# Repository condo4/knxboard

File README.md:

# KnxBoard

A compact 4-layer PCB that connects an STM32 microcontroller to the KNX home automation bus via the NCN5130 transceiver IC.

## Overview

KnxBoard integrates an STM32G491KEU6 (ARM Cortex-M4, 170 MHz) with an NCN5130MNTWG KNX TP transceiver. The NCN5130 handles the KNX physical and MAC layers and provides on-board power regulation from the KNX bus voltage, so the board requires no external power supply when connected to a KNX installation.

**Board version:** V5.0  
**PCB size:** 35.75 × 33.75 mm, 4 layers, 1.6 mm thickness  
**Manufactured by:** JLCPCB

## Key Components

| Reference | Part | Description |
|-----------|------|-------------|
| IC1 | STM32G491KEU6 | ARM Cortex-M4, 170 MHz, 512 KB Flash, 112 KB SRAM, UFQFPN32 |
| IC2 | NCN5130MNTWG | KNX certified TP transceiver (TP1-256), 9600 Bd, integrated DC-DC |
| Y1 | 16 MHz crystal | MCU clock source |
| D1 | SS16T3G | Schottky diode |
| D2 | SMAJ40CA | 40 V bidirectional TVS, KNX bus protection |
| D3 | LED | KNX programming indicator |
| SW1 | Push button | KNX programming button |

## Connectors

| Reference | Function |
|-----------|----------|
| J1 | KNX bus (2-pin) |
| J2 | SWD debug/programming (2×3) |
| J3 | RS485 / 1-Wire interface (10-pin) |
| J4 | Auxiliary / expansion (10-pin) |

## MCU Pin Assignment

| Signal | Pin | Peripheral | Description |
|--------|-----|------------|-------------|
| KNX_TX | PA2 | LPUART1_TX | KNX data transmit to NCN5130 |
| KNX_RX | PA3 | LPUART1_RX | KNX data receive from NCN5130 |
| KNX_PROG_BTN | PA0 | GPIO_Input | Programming mode button |
| KNX_SAVEB | PA1 | GPIO_Input | Save-B input from NCN5130 |
| KNX_PROG_LED | PF1 | GPIO_Output | Programming mode LED |
| RS437/W1_TX | PA9 | USART1_TX | RS485 / 1-Wire transmit |
| RS437/W1_RX | PA10 | USART1_RX | RS485 / 1-Wire receive |
| DEBUG_TX | PB3 | USART2_TX | Debug UART transmit |
| DEBUG_RX | PA15 | USART2_RX | Debug UART receive |
| SWDIO | PA13 | SYS_JTMS | SWD data |
| SWCLK | PA14 | SYS_JTCK | SWD clock |

ADC2 monitors internal signals (bus voltage/current supervision via NCN5130).

## Power Architecture

The NCN5130 converts KNX bus voltage (21–29 V DC) internally:

- **DC-DC1:** Fixed 3.3 V — powers the STM32 and board logic
- **DC-DC2:** Adjustable 1.2–21 V — configurable auxiliary rail
- **Linear regulator:** 20 V — internal NCN5130 supply

The board draws up to 40 mA from the KNX bus.

## PCB Stackup

| Layer | Function |
|-------|----------|
| F.Cu | Signal + components (all 44 footprints on front) |
| In1.Cu | Ground plane |
| In2.Cu | Power plane (3.3 V / 12 V) |
| B.Cu | Signal |

## Firmware

The `CubeMX/` directory contains the STM32CubeMX project (`CubeMX.ioc`) used to generate HAL initialization code.

- **Toolchain:** GCC / Makefile
- **HAL package:** STM32Cube FW_G4 V1.5.1
- **Active peripherals:** LPUART1 (KNX), USART1 (RS485/1-Wire), USART2 (debug), TIM6, ADC2, SWD

## Repository Structure

```
KnxBoard/
├── KnxBoard.kicad_sch       # Schematic
├── KnxBoard.kicad_pcb       # PCB layout
├── KnxBoard.kicad_pro       # KiCad project
├── CubeMX/                  # STM32CubeMX project
│   └── CubeMX.ioc
├── Library.pretty/          # Custom KiCad footprints
│   ├── NCN5130MNTWG.kicad_mod
│   └── STM32G491KEU6.kicad_mod
├── datasheet/               # Component datasheets
├── JLCPCB_KNXBOARD_V5.0_1.zip  # Gerbers / manufacturing files
└── KnxBoard-backups/        # KiCad auto-backups
```

## Tools

- [KiCad 9](https://www.kicad.org/) — schematic and PCB design
- [STM32CubeMX 6.8](https://www.st.com/en/development-tools/stm32cubemx.html) — MCU peripheral configuration
- [STM32CubeIDE](https://www.st.com/en/development-tools/stm32cubeide.html) or `arm-none-eabi-gcc` — firmware build

## References

- [NCN5130 Datasheet](datasheet/NCN5130-D.PDF)
- [STM32G491KE Datasheet](datasheet/STM32G491KE_Datasheet.pdf)
- [STM32G491KE Reference Manual](datasheet/STM32G491KE_RefManual.pdf)

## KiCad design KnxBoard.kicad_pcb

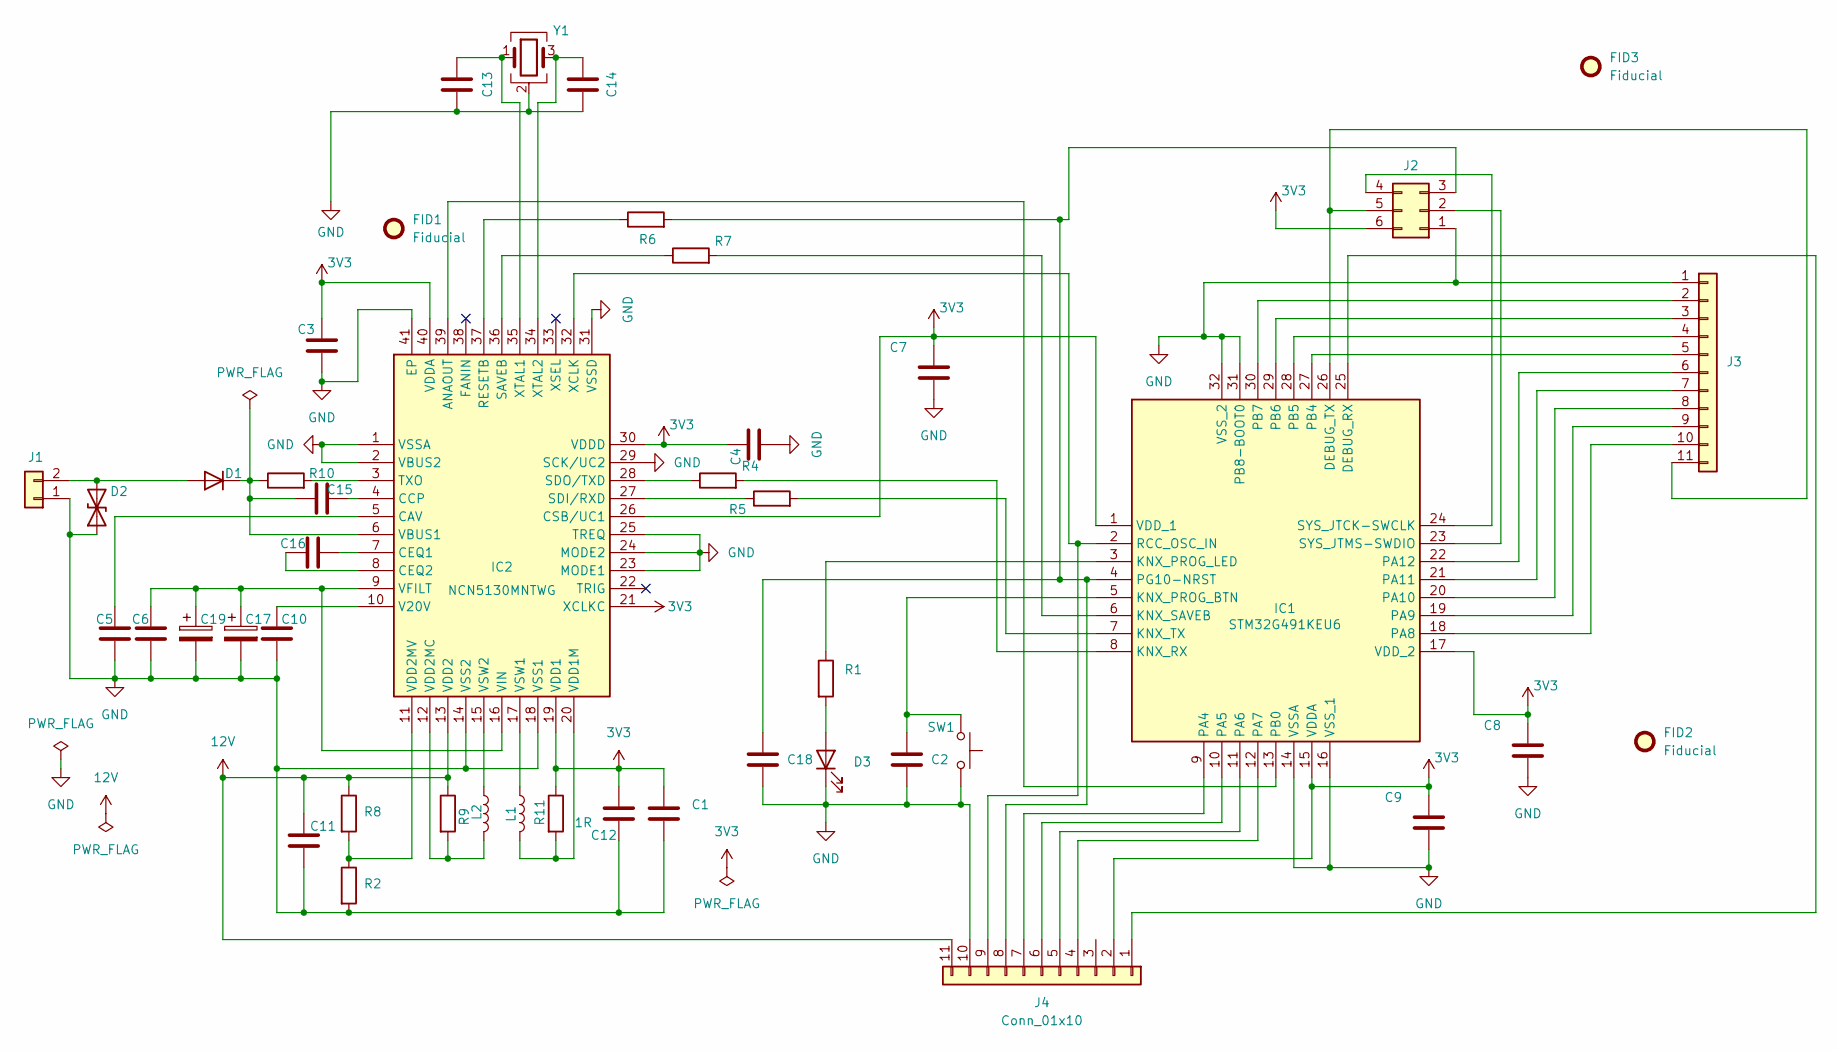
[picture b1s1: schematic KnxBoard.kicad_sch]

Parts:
C1, C2, C3, C4, C5, C6, C7, C8, C9, C18: 0.1 uF 50 VDC 5% 0402 X7S; C_0402_1005Metric; Mouser Part Number 81-GRM155C71H104JE9D
C10: 1 uF 100 VDC 10% 0805 X7S; C_0805_2012Metric; Mouser Part Number 81-GRJ21BC72A105KE1L
C11: 22 uF 25 VDC 0805 X5R; C_0805_2012Metric; Mouser Part Number 81-GRM21BC71C106KE1K
C12: 10 uF 16 VDC 10% 0805 X7S; C_0805_2012Metric; Mouser Part Number 81-GRM21BC71C106KE1K
C13, C14: 10 pF 50 VDC 5% 0402 C0G; C_0402_1005Metric; Mouser Part Number 81-GRM1555C1H100JA01D
C15: 0.047 uF 50 VDC 5% 0402 X7S; C_0402_1005Metric; Mouser Part Number 81-GRM155C71H473JE9D
C16: 0.22 uF 50 VDC 10% 0805 X7R; C_0805_2012Metric; Mouser Part Number 81-GCM21BR71H224KA7K
C17, C19: 100uF 35 Volt; CP_Elec_6.3x7.7; Mouser Part Number 661-EMZA350A101MF80S
D1: SS16T3G; D_SMA; Mouser Part Number 863-SS16T3G
D2: SMAJ40CA; D_SMA; Mouser Part Number 652-SMAJ40CA
D3: LED; LED_0603_1608Metric; Mouser Part Number 710-150060RS55040
FID1, FID2, FID3: Fiducial; Fiducial_1mm_Mask2mm
IC1: STM32G491KEU6; UQFN-32_5x5mm_P0.5mm; Mouser Part Number 511-STM32G491KEU6
IC2: NCN5130MNTWG; QFN50P600X600X100-41N; Manufacturer_Part_Number NCN5130MNTWG; Mouser Part Number 863-NCN5130MNTWG
J1: Conn_01x02; KNX_Connector
J2: Conn_02x03_Counter_Clockwise; PinHeader_2x03_P1.27mm_Vertical
J3, J4: Conn_01x10; PinHeader_1x11_P2.54mm_Vertical
L1, L2: 220 uH 0.4A; L_1008_2520Metric; Mouser Part Number 963-LB2518T221M
R1: 100; R_0402_1005Metric; Mouser Part Number 594-MCS04020C1000FE0
R2: 20k; R_0402_1005Metric; Mouser Part Number 594-MCS04020C2002FE0
R4, R5, R6, R7: 0; R_0402_1005Metric; Mouser Part Number 594-MCS04020Z0000ZE0
R8: 180k; R_0402_1005Metric; Mouser Part Number 594-MCS04020C1803FE0
R9, R11: 1R; R_0402_1005Metric; Mouser Part Number 594-MCS0402MC1008FE5
R10: 27 1W; R_2512_6332Metric; Mouser Part Number 660-WK73R2BTTD27R0F
SW1: SW_Push; SW_SPST_SKQG_WithStem; Mouser Part Number 688-SKQGAB
Y1: 16MHz; Crystal_SMD_3225-4Pin_3.2x2.5mm; Mouser Part Number 732-FA238-16B-K3

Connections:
3V3: C1.1, C3.1, C4.1, C7.1, C8.1, C9.1, C12.1, IC1.1 (VDD_1), IC1.15 (VDDA), IC1.17 (VDD_2), IC2.19 (VDD1), IC2.21 (XCLKC), IC2.26 (CSB/UC1), IC2.30 (VDDD), IC2.40 (VDDA), J2.6, J4.2, R11.1
12V: C11.1, IC2.13 (VDD2), J4.11, R8.1, R9.1
GND: C1.2, C2.2, C3.2, C4.2, C5.2, C6.2, C7.2, C8.2, C9.2, C10.2, C11.2, C12.2, C13.2, C14.2, C17.2, C18.2, C19.2, D2.1 (A1), D3.1 (K), IC1.14 (VSSA), IC1.16 (VSS_1), IC1.31 (PB8-BOOT0), IC1.32 (VSS_2), IC2.1 (VSSA), IC2.2 (VBUS2), IC2.14 (VSS2), IC2.18 (VSS1), IC2.23 (MODE1), IC2.24 (MODE2), IC2.25 (TREQ), IC2.29 (SCK/UC2), IC2.31 (VSSD), IC2.41 (EP), J1.1, J2.1, J3.1, J4.10, R2.2, SW1.2, Y1.2 (G), Y1.4 (G)
unnamed: D1.2 (A), D2.2 (A2), J1.2
unnamed: C15.1, D1.1 (K), IC2.6 (VBUS1), R10.1
unnamed: D3.2 (A), R1.2
unnamed: IC1.25 (DEBUG_RX), J4.1
unnamed: IC1.26 (DEBUG_TX), J2.5, J3.11
unnamed: C2.1, IC1.5 (KNX_PROG_BTN), SW1.1
unnamed: IC1.3 (KNX_PROG_LED), R1.1
unnamed: IC1.8 (KNX_RX), R4.2
unnamed: IC1.6 (KNX_SAVEB), R7.2
unnamed: IC1.7 (KNX_TX), R5.2
unnamed: IC1.9 (PA4), J4.7
unnamed: IC1.10 (PA5), J4.6
unnamed: IC1.11 (PA6), J4.5
unnamed: IC1.12 (PA7), J4.4
unnamed: IC1.18 (PA8), J3.10
unnamed: IC1.19 (PA9), J3.9
unnamed: IC1.20 (PA10), J3.8
unnamed: IC1.21 (PA11), J3.7
unnamed: IC1.22 (PA12), J3.6
unnamed: IC1.13 (PB0), IC2.39 (ANAOUT)
unnamed: IC1.27 (PB4), J3.5
unnamed: IC1.28 (PB5), J3.4
unnamed: IC1.29 (PB6), J3.3
unnamed: IC1.30 (PB7), J3.2
unnamed: C18.1, IC1.4 (PG10-NRST), J2.3, J4.8, R6.2
unnamed: IC1.2 (RCC_OSC_IN), IC2.32 (XCLK), J4.9
unnamed: IC1.24 (SYS_JTCK-SWCLK), J2.4
unnamed: IC1.23 (SYS_JTMS-SWDIO), J2.2
unnamed: C5.1, IC2.5 (CAV)
unnamed: C15.2, IC2.4 (CCP)
unnamed: C16.2, IC2.7 (CEQ1)
unnamed: C16.1, IC2.8 (CEQ2)
unnamed: IC2.37 (RESETB), R6.1
unnamed: IC2.36 (SAVEB), R7.1
unnamed: IC2.27 (SDI/RXD), R5.1
unnamed: IC2.28 (SDO/TXD), R4.1
unnamed: IC2.3 (TXO), R10.2
unnamed: C10.1, IC2.10 (V20V)
unnamed: IC2.20 (VDD1M), L1.2, R11.2
unnamed: IC2.12 (VDD2MC), L2.2, R9.2
unnamed: IC2.11 (VDD2MV), R2.1, R8.2
unnamed: C6.1, C17.1, C19.1, IC2.9 (VFILT), IC2.16 (VIN)
unnamed: IC2.17 (VSW1), L1.1
unnamed: IC2.15 (VSW2), L2.1
unnamed: C13.1, IC2.35 (XTAL1), Y1.1
unnamed: C14.1, IC2.34 (XTAL2), Y1.3

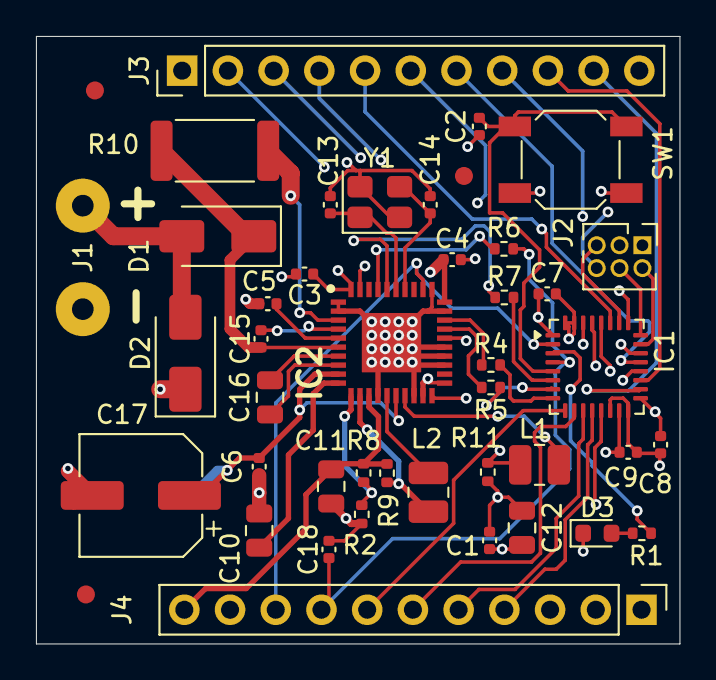
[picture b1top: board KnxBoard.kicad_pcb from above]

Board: 4 copper layers, 35.8 x 33.8 mm, 45 parts (1 on the bottom side), 49 nets.

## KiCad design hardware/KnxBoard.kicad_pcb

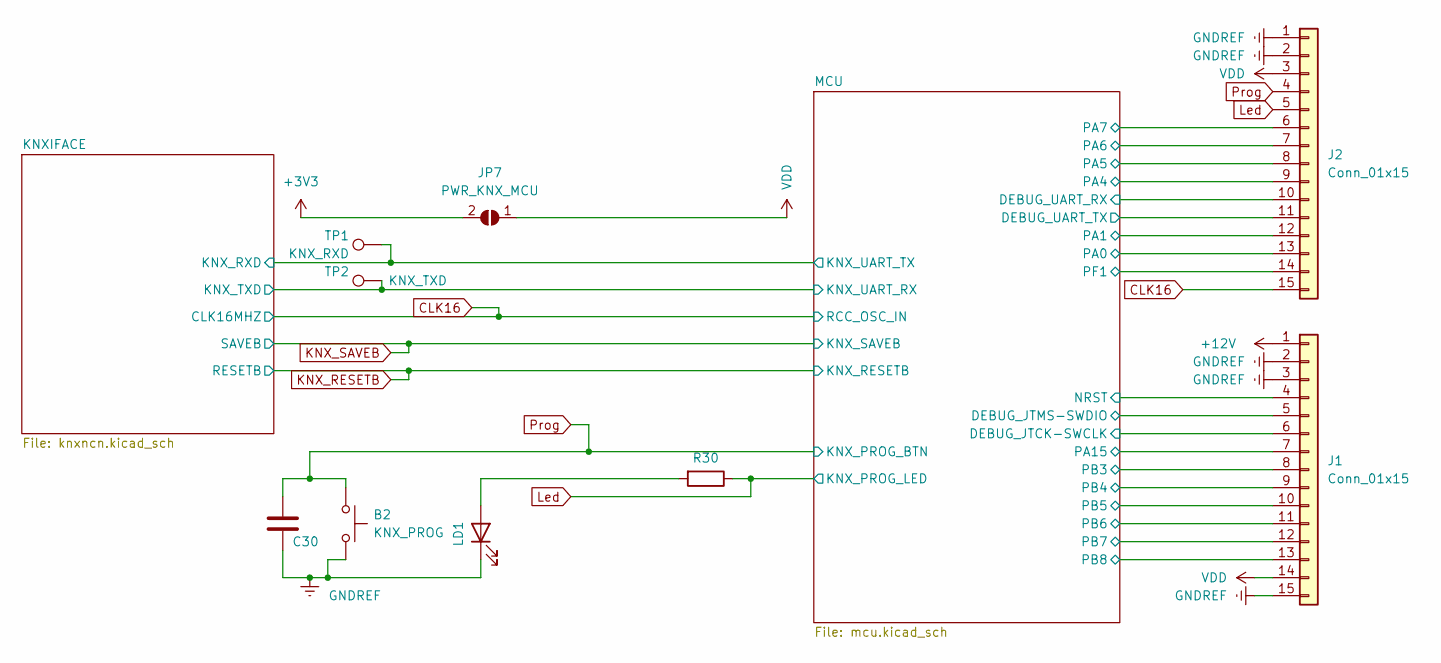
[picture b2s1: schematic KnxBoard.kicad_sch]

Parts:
B2: KNX_PROG; SW_SPST_SKQG_WithStem
C30: 100nF 6.3V; C_0603_1608Metric_Pad1.08x0.95mm_HandSolder; MPN CL10B104KA8NNWC
J1, J2: Conn_01x15; PinHeader_1x15_P2.54mm_Vertical
JP7: PWR_KNX_MCU; SolderJumper-2_P1.3mm_Open_TrianglePad1.0x1.5mm
LD1: LED; LED_0603_1608Metric; MPN 150060RS55040
R30: 100R; R_0603_1608Metric; MPN MCT06030C1000FP500
TP1: KNX_RXD; TestPoint_Pad_D1.0mm
TP2: KNX_TXD; TestPoint_Pad_D1.0mm

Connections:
+3V3: JP7.2 (B); also elsewhere on the board
+12V: J1.1; also elsewhere on the board
/KNXIFACE/KNX_RXD: TP1.1; also elsewhere on the board
/KNXIFACE/KNX_TXD: TP2.1; also elsewhere on the board
/MCU/DEBUG_JTCK-SWCLK: J1.6; also elsewhere on the board
/MCU/DEBUG_JTMS-SWDIO: J1.5; also elsewhere on the board
/MCU/DEBUG_UART_RX: J2.10; also elsewhere on the board
/MCU/DEBUG_UART_TX: J2.11; also elsewhere on the board
/MCU/NRST: J1.4; also elsewhere on the board
/MCU/PA0: J2.13; also elsewhere on the board
/MCU/PA1: J2.12; also elsewhere on the board
/MCU/PA4: J2.9; also elsewhere on the board
/MCU/PA5: J2.8; also elsewhere on the board
/MCU/PA6: J2.7; also elsewhere on the board
/MCU/PA7: J2.6; also elsewhere on the board
/MCU/PA15: J1.7; also elsewhere on the board
/MCU/PB3: J1.8; also elsewhere on the board
/MCU/PB4: J1.9; also elsewhere on the board
/MCU/PB5: J1.10; also elsewhere on the board
/MCU/PB6: J1.11; also elsewhere on the board
/MCU/PB7: J1.12; also elsewhere on the board
/MCU/PB8: J1.13; also elsewhere on the board
/MCU/PF1: J2.14; also elsewhere on the board
CLK16: J2.15; also elsewhere on the board
GNDREF: B2.2, C30.2, J1.2, J1.3, J1.15, J2.1, J2.2, LD1.1 (K); also elsewhere on the board
Led: J2.5, R30.1; also elsewhere on the board
unnamed: LD1.2 (A), R30.2
Prog: B2.1, C30.1, J2.4; also elsewhere on the board
VDD: J1.14, J2.3, JP7.1 (A); also elsewhere on the board

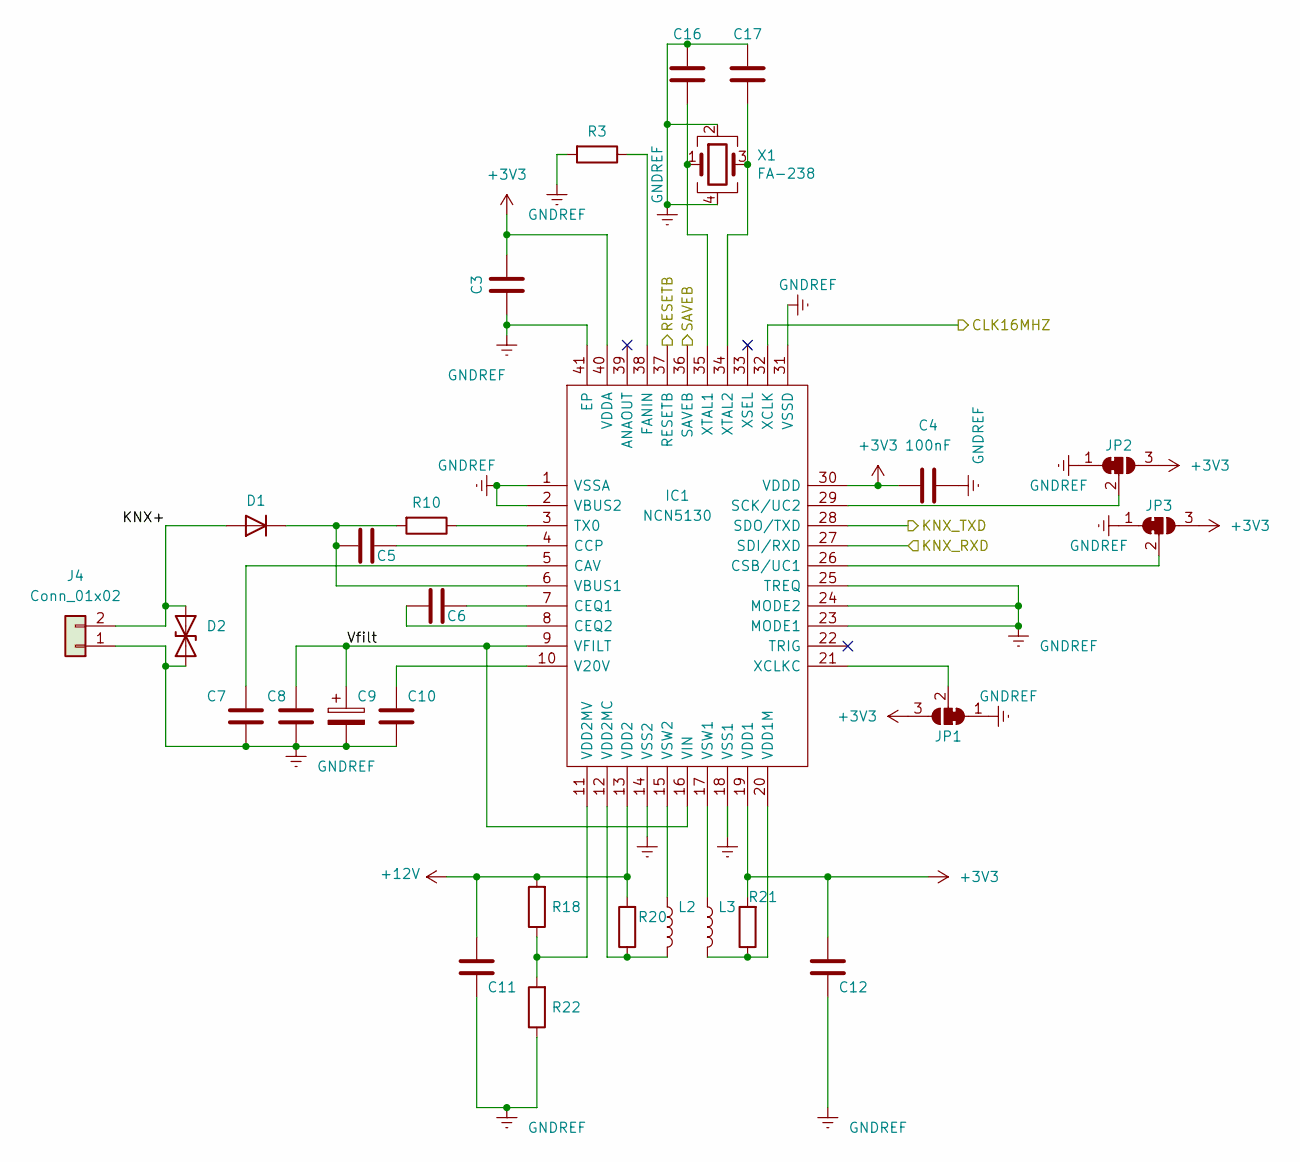
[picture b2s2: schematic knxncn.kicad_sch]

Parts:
C3: 100nF 6.3V; C_0603_1608Metric_Pad1.08x0.95mm_HandSolder; MPN CL10B104KA8NNWC
C4: 100nF; C_0603_1608Metric_Pad1.08x0.95mm_HandSolder
C5: 47nF 50V; C_0603_1608Metric_Pad1.08x0.95mm_HandSolder; MPN CL10B473KB8NNND
C6: 220nF 50V; C_0603_1608Metric_Pad1.08x0.95mm_HandSolder; MPN CL10A224KB8NNNC
C7, C8: 100nF 50V; C_0603_1608Metric_Pad1.08x0.95mm_HandSolder; MPN CL10B104KB8NFNC
C9: 100uF 35V; CP_Elec_6.3x7.7
C10: 1uF 50V ESR < 2ohm; C_0603_1608Metric_Pad1.08x0.95mm_HandSolder; MPN CL10A105KL8NNNC
C11, C12: 10uF 6.3V ESR < 0.1ohm; C_0805_2012Metric_Pad1.18x1.45mm_HandSolder; MPN CL21A106KOQNNNG
C16, C17: 10pF 6.3V; C_0603_1608Metric_Pad1.08x0.95mm_HandSolder; MPN CL10C100DB81PNC
D1: SS16T3G; D_SMA; MPN SS16T3G
D2: 1SMA40CA; D_SMA
IC1: NCN5130; Manufacturer_Part_Number NCN5130; Mouser Part Number N/A
J4: Conn_01x02; KNX_Connector
JP1: Clock_8_16; SolderJumper-3_P1.3mm_Open_RoundedPad1.0x1.5mm
JP2: Parity; SolderJumper-3_P1.3mm_Open_RoundedPad1.0x1.5mm
JP3: Speed; SolderJumper-3_P1.3mm_Open_RoundedPad1.0x1.5mm
L2, L3: 220uH; L_1008_2520Metric; MPN LB2518T221M
R3: NOTMOUNT; R_0603_1608Metric
R10: 27R 1W; R_0612_1632Metric; MPN WK73R2BTTD27R0F
R18: 56K 1/16w; R_0603_1608Metric; MPN RT0603DRE0756KL
R20, R21: 1R 1/16W; R_0603_1608Metric; MPN SFR03EZPJ1R0
R22: 499K 1/16w; R_0603_1608Metric; MPN RT0603FRE07499KL
X1: FA-238; Crystal_SMD_SeikoEpson_FA238-4Pin_3.2x2.5mm; MPN FA-238 16.0000MB-K3

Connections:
+3V3: C3.2, C4.1, C12.1, IC1.19 (VDD1), IC1.30 (VDDD), IC1.40 (VDDA), JP1.3 (B), JP2.3 (B), JP3.3 (B), R21.2; also elsewhere on the board
+12V: C11.1, IC1.13 (VDD2), R18.2, R20.2; also elsewhere on the board
/KNXIFACE/KNX+: D1.2 (A), D2.2 (A2), J4.2
/KNXIFACE/KNX_RXD: IC1.27 (SDI/RXD); also elsewhere on the board
/KNXIFACE/KNX_TXD: IC1.28 (SDO/TXD); also elsewhere on the board
/KNXIFACE/Vfilt: C8.1, C9.1, IC1.9 (VFILT), IC1.16 (VIN)
CLK16: IC1.32 (XCLK); also elsewhere on the board
GNDREF: C3.1, C4.2, C7.2, C8.2, C9.2, C10.2, C11.2, C12.2, C16.1, C17.1, D2.1 (A1), IC1.1 (VSSA), IC1.2 (VBUS2), IC1.14 (VSS2), IC1.18 (VSS1), IC1.23 (MODE1), IC1.24 (MODE2), IC1.25 (TREQ), IC1.31 (VSSD), IC1.41 (EP), J4.1, JP1.1 (A), JP2.1 (A), JP3.1 (A), R3.2, R22.1, X1.2, X1.4; also elsewhere on the board
KNX_RESETB: IC1.37 (RESETB); also elsewhere on the board
KNX_SAVEB: IC1.36 (SAVEB); also elsewhere on the board
unnamed: C5.1, IC1.4 (CCP)
unnamed: C5.2, D1.1 (K), IC1.6 (VBUS1), R10.2
unnamed: C6.1, IC1.7 (CEQ1)
unnamed: C6.2, IC1.8 (CEQ2)
unnamed: C7.1, IC1.5 (CAV)
unnamed: C10.1, IC1.10 (V20V)
unnamed: C16.2, IC1.35 (XTAL1), X1.1
unnamed: C17.2, IC1.34 (XTAL2), X1.3
unnamed: IC1.3 (TX0), R10.1
unnamed: IC1.11 (VDD2MV), R18.1, R22.2
unnamed: IC1.12 (VDD2MC), L2.2, R20.1
unnamed: IC1.15 (VSW2), L2.1
unnamed: IC1.17 (VSW1), L3.1
unnamed: IC1.20 (VDD1M), L3.2, R21.1
unnamed: IC1.21 (XCLKC), JP1.2 (C)
unnamed: IC1.26 (CSB/UC1), JP3.2 (C)
unnamed: IC1.29 (SCK/UC2), JP2.2 (C)
unnamed: IC1.38 (FANIN), R3.1

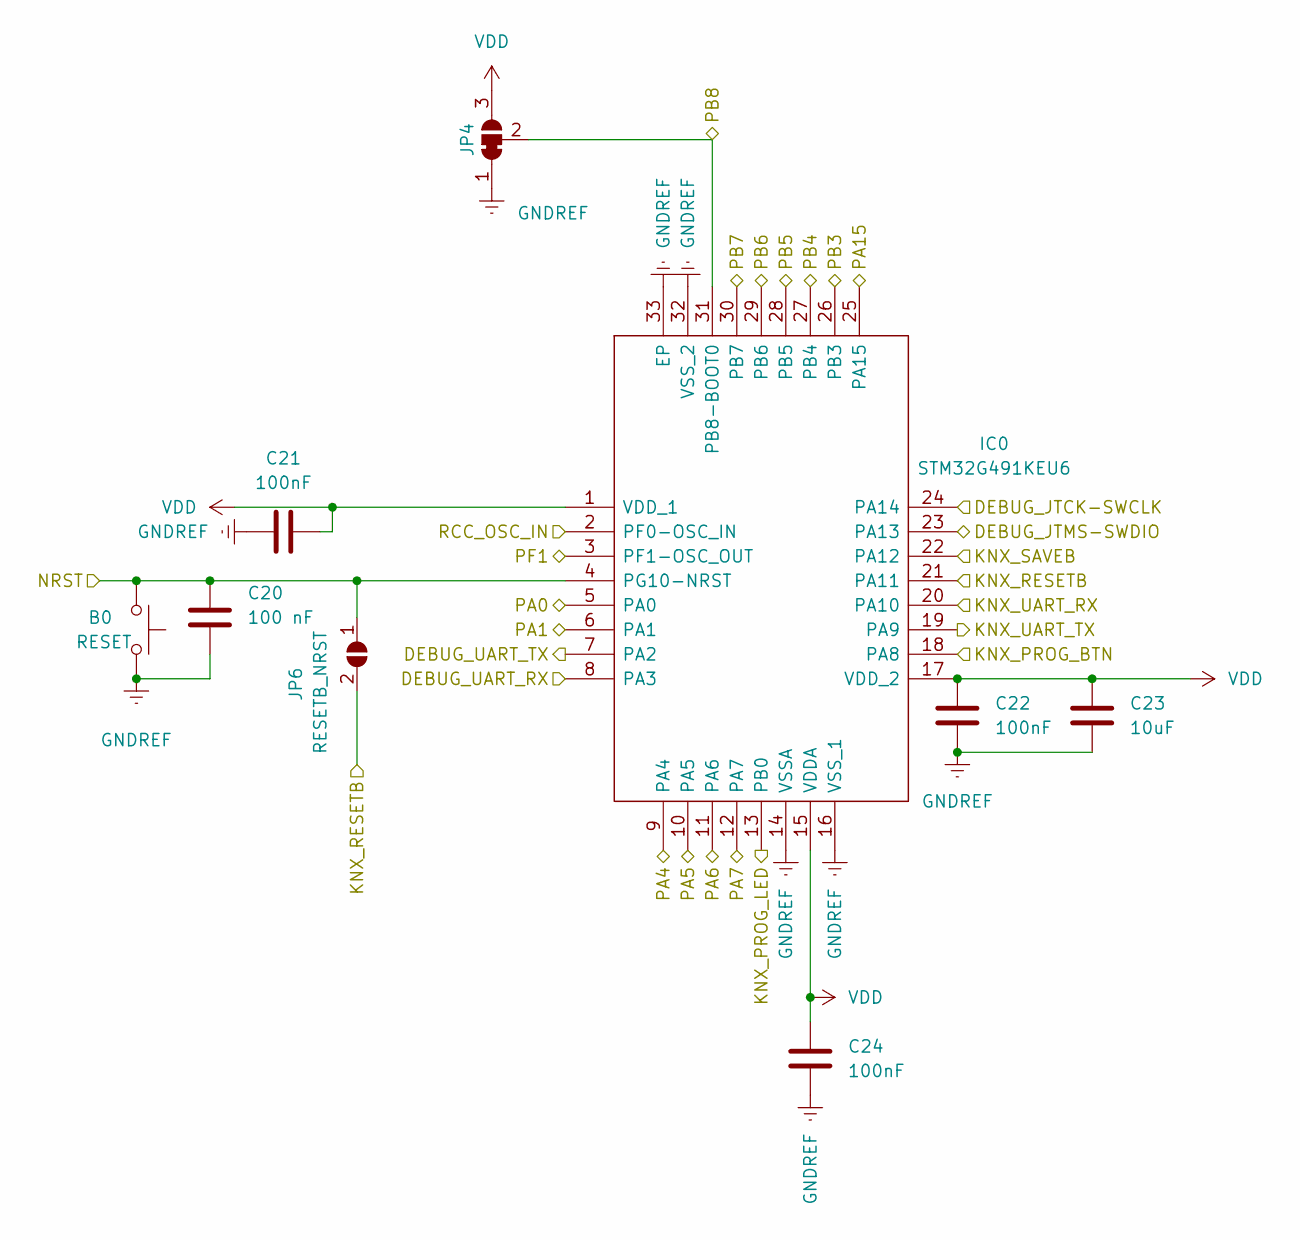
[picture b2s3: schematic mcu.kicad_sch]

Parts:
B0: RESET; SW_SPST_SKQG_WithStem
C20: 100 nF; C_0603_1608Metric_Pad1.08x0.95mm_HandSolder
C21, C22, C24: 100nF; C_0603_1608Metric_Pad1.08x0.95mm_HandSolder
C23: 10uF; C_0603_1608Metric_Pad1.08x0.95mm_HandSolder
IC0: STM32G491KEU6; QFN50P500X500X60-33N-D; Mouser Part Number 511-STM32G491KEU6
JP4: BootMode; SolderJumper-3_P1.3mm_Open_RoundedPad1.0x1.5mm
JP6: RESETB_NRST; SolderJumper-2_P1.3mm_Open_TrianglePad1.0x1.5mm

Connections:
/KNXIFACE/KNX_RXD: IC0.19 (PA9); also elsewhere on the board
/KNXIFACE/KNX_TXD: IC0.20 (PA10); also elsewhere on the board
/MCU/DEBUG_JTCK-SWCLK: IC0.24 (PA14); also elsewhere on the board
/MCU/DEBUG_JTMS-SWDIO: IC0.23 (PA13); also elsewhere on the board
/MCU/DEBUG_UART_RX: IC0.8 (PA3); also elsewhere on the board
/MCU/DEBUG_UART_TX: IC0.7 (PA2); also elsewhere on the board
/MCU/NRST: B0.1, C20.1, IC0.4 (PG10-NRST), JP6.1 (A); also elsewhere on the board
/MCU/PA0: IC0.5 (PA0); also elsewhere on the board
/MCU/PA1: IC0.6 (PA1); also elsewhere on the board
/MCU/PA4: IC0.9 (PA4); also elsewhere on the board
/MCU/PA5: IC0.10 (PA5); also elsewhere on the board
/MCU/PA6: IC0.11 (PA6); also elsewhere on the board
/MCU/PA7: IC0.12 (PA7); also elsewhere on the board
/MCU/PA15: IC0.25 (PA15); also elsewhere on the board
/MCU/PB3: IC0.26 (PB3); also elsewhere on the board
/MCU/PB4: IC0.27 (PB4); also elsewhere on the board
/MCU/PB5: IC0.28 (PB5); also elsewhere on the board
/MCU/PB6: IC0.29 (PB6); also elsewhere on the board
/MCU/PB7: IC0.30 (PB7); also elsewhere on the board
/MCU/PB8: IC0.31 (PB8-BOOT0), JP4.2 (C); also elsewhere on the board
/MCU/PF1: IC0.3 (PF1-OSC_OUT); also elsewhere on the board
CLK16: IC0.2 (PF0-OSC_IN); also elsewhere on the board
GNDREF: B0.2, C20.2, C21.1, C22.2, C23.2, C24.2, IC0.14 (VSSA), IC0.16 (VSS_1), IC0.32 (VSS_2), IC0.33 (EP), JP4.1 (A); also elsewhere on the board
KNX_RESETB: IC0.21 (PA11), JP6.2 (B); also elsewhere on the board
KNX_SAVEB: IC0.22 (PA12); also elsewhere on the board
Led: IC0.13 (PB0); also elsewhere on the board
Prog: IC0.18 (PA8); also elsewhere on the board
VDD: C21.2, C22.1, C23.1, C24.1, IC0.1 (VDD_1), IC0.15 (VDDA), IC0.17 (VDD_2), JP4.3 (B); also elsewhere on the board

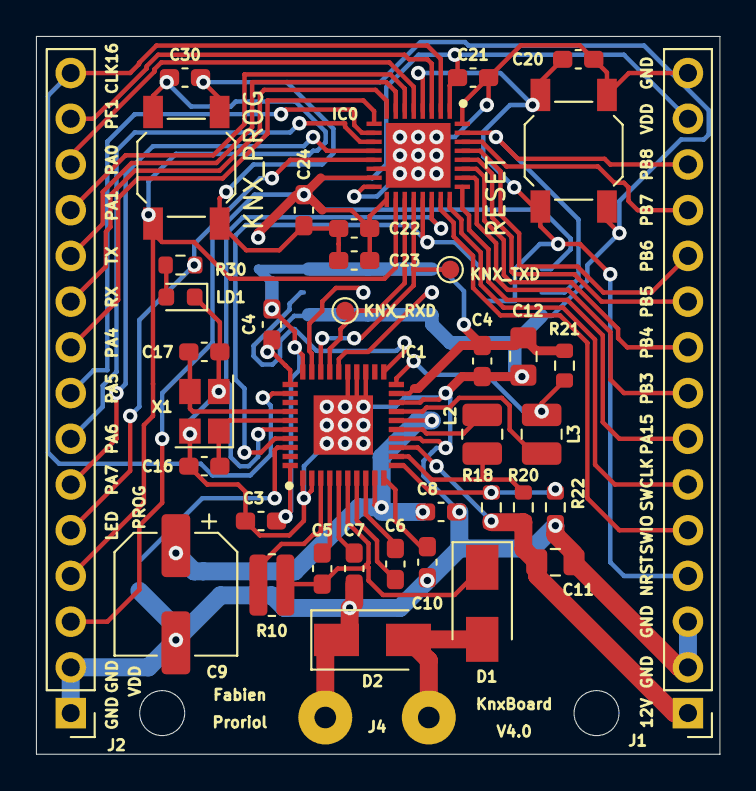
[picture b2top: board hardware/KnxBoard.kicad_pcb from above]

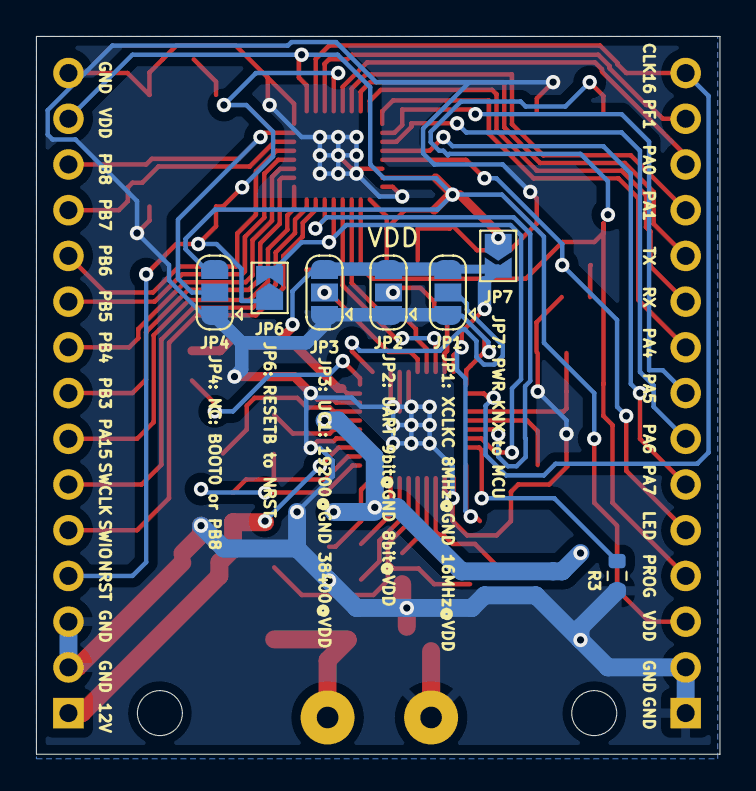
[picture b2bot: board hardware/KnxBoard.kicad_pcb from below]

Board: 2 copper layers, 38.0 x 39.9 mm, 47 parts (7 on the bottom side), 51 nets.

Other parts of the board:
C4#2: 100nF; C_0603_1608Metric_Pad1.08x0.95mm_HandSolder

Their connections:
+3V3: C4#2.1; also elsewhere on the board
GNDREF: C4#2.2; also elsewhere on the board

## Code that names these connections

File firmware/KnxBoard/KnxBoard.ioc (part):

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Mcu.Name=STM32G491K(C-E)Ux
Mcu.Package=UFQFPN32
Mcu.UserName=STM32G491KEUx
PA10.Mode=Asynchronous
PA10.Signal=USART1_RX
PA11.GPIOParameters=GPIO_Label
PA11.GPIO_Label=KNX_RESETB
PA11.Signal=GPXTI11
PA12.GPIOParameters=GPIO_Label
PA12.GPIO_Label=KNX_SAVEB
PA12.Signal=GPXTI12
PA13.Mode=JTAG_5_pins
PA13.Signal=SYS_JTMS-SWDIO
PA14.Mode=JTAG_5_pins
PA14.Signal=SYS_JTCK-SWCLK
PA15.Mode=JTAG_5_pins
PA15.Signal=SYS_JTDI
PA2.Mode=Asynchronous
PA2.Signal=USART2_TX
PA3.Mode=Asynchronous
PA3.Signal=USART2_RX
PA8.GPIOParameters=GPIO_Label
PA8.GPIO_Label=KNX_PROG_BTN
PA8.Signal=GPXTI8
PA9.Mode=Asynchronous
PA9.Signal=USART1_TX
PB0.GPIOParameters=GPIO_Label
PB0.GPIO_Label=KNX_PROG_LED
PB0.Signal=GPIO_Output
PB3.Mode=JTAG_5_pins
PB3.Signal=SYS_JTDO-SWO
PB4.Mode=JTAG_5_pins
PB4.Signal=SYS_JTRST
PF0-OSC_IN.Mode=HSE-External-Clock-Source
PF0-OSC_IN.Signal=RCC_OSC_IN
RCC.HSE_VALUE=8000000
RCC.SYSCLKFreq_VALUE=16000000
board=custom

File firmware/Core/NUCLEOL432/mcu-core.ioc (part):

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Mcu.Name=STM32L432K(B-C)Ux
Mcu.Package=UFQFPN32
Mcu.UserName=STM32L432KCUx
PA0.GPIOParameters=GPIO_Label
PA0.GPIO_Label=MCO [High speed clock in]
PA0.Mode=HSE-External-Clock-Source-for-LittleOrca
PA0.Signal=RCC_CK_IN
PA10.GPIOParameters=GPIO_Speed,GPIO_Label
PA10.GPIO_Label=KNX_RX
PA10.GPIO_Speed=GPIO_SPEED_FREQ_MEDIUM
PA10.Mode=Asynchronous
PA10.Signal=USART1_RX
PA11.GPIOParameters=GPIO_PuPd,GPIO_Label
PA11.GPIO_Label=KNX_PROG_BTN
PA11.GPIO_PuPd=GPIO_PULLDOWN
PA11.Signal=GPXTI11
PA13\ (JTMS-SWDIO).GPIOParameters=GPIO_Label
PA13\ (JTMS-SWDIO).GPIO_Label=SWDIO
PA13\ (JTMS-SWDIO).Mode=Serial_Wire
PA13\ (JTMS-SWDIO).Signal=SYS_JTMS-SWDIO
PA14\ (JTCK-SWCLK).GPIOParameters=GPIO_Label
PA14\ (JTCK-SWCLK).GPIO_Label=SWCLK
PA14\ (JTCK-SWCLK).Mode=Serial_Wire
PA14\ (JTCK-SWCLK).Signal=SYS_JTCK-SWCLK
PA15\ (JTDI).GPIOParameters=GPIO_Label
PA15\ (JTDI).GPIO_Label=DEBUG_RX
PA15\ (JTDI).Mode=Asynchronous
PA15\ (JTDI).Signal=USART2_RX
PA2.GPIOParameters=GPIO_Label
PA2.GPIO_Label=DEBUG_TX
PA2.Mode=Asynchronous
PA2.Signal=USART2_TX
PA3.Signal=ADCx_IN8
PA4.Signal=ADCx_IN9
PA5.Signal=ADCx_IN10
PA6.Signal=ADCx_IN11
PA9.GPIOParameters=GPIO_Speed,GPIO_Label
PA9.GPIO_Label=KNX_TX
PA9.GPIO_Speed=GPIO_SPEED_FREQ_MEDIUM
PA9.Mode=Asynchronous
PA9.Signal=USART1_TX
PB3\ (JTDO-TRACESWO).GPIOParameters=GPIO_Label
PB3\ (JTDO-TRACESWO).GPIO_Label=KNX_PROG_LED
PB3\ (JTDO-TRACESWO).Signal=GPIO_Output
PC14-OSC32_IN\ (PC14).Mode=LSE-External-Oscillator
PC14-OSC32_IN\ (PC14).Signal=RCC_OSC32_IN
PC15-OSC32_OUT\ (PC15).Mode=LSE-External-Oscillator
PC15-OSC32_OUT\ (PC15).Signal=RCC_OSC32_OUT
RCC.HSE_VALUE=8000000
RCC.SYSCLKFreq_VALUE=64000000
RCC.SYSCLKSource=RCC_SYSCLKSOURCE_PLLCLK
board=NUCLEO-L432KC
boardIOC=true

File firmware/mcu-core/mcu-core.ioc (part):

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Mcu.Name=STM32U575CITx
Mcu.Package=LQFP48
Mcu.UserName=STM32U575CITx
PA10.GPIOParameters=GPIO_Label
PA10.GPIO_Label=DEBUG_UART_RX
PA10.Mode=Asynchronous
PA10.Signal=USART1_RX
PA13\ (JTMS/SWDIO).Mode=JTAG_5_pins
PA13\ (JTMS/SWDIO).Signal=DEBUG_JTMS-SWDIO
PA14\ (JTCK/SWCLK).Mode=JTAG_5_pins
PA14\ (JTCK/SWCLK).Signal=DEBUG_JTCK-SWCLK
PA15\ (JTDI).Mode=JTAG_5_pins
PA15\ (JTDI).Signal=DEBUG_JTDI
PA2.GPIOParameters=GPIO_Label
PA2.GPIO_Label=KNX_UART_TX
PA2.Mode=Asynchronous
PA2.Signal=USART2_TX
PA3.GPIOParameters=GPIO_Label
PA3.GPIO_Label=KNX_UART_RX
PA3.Mode=Asynchronous
PA3.Signal=USART2_RX
PA9.GPIOParameters=GPIO_Label
PA9.GPIO_Label=DEBUG_UART_TX
PA9.Mode=Asynchronous
PA9.Signal=USART1_TX
PB10.Signal=GPXTI10
PB2.Signal=GPXTI2
PB3\ (JTDO/TRACESWO).Mode=JTAG_5_pins
PB3\ (JTDO/TRACESWO).Signal=DEBUG_JTDO-SWO
PB4\ (NJTRST).Mode=JTAG_5_pins
PB4\ (NJTRST).Signal=DEBUG_JTRST
PC13.GPIOParameters=GPIO_Label
PC13.GPIO_Label=KNX_PROG_LED
PC13.Signal=GPIO_Output
PC14-OSC32_IN\ (PC14).GPIOParameters=GPIO_Label
PC14-OSC32_IN\ (PC14).GPIO_Label=KNX_PROG_BTN
PC14-OSC32_IN\ (PC14).Signal=GPIO_Input
PH0-OSC_IN\ (PH0).Mode=HSE-External-Clock-Source
PH0-OSC_IN\ (PH0).Signal=RCC_OSC_IN
RCC.HSE_VALUE=16000000
board=custom

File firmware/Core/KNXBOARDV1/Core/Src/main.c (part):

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  GPIO_InitStruct.Pull = GPIO_NOPULL;
  HAL_GPIO_Init(GPIOC, &GPIO_InitStruct);

  /*Configure GPIO pins : PA0 PA4 PA5 PA6
                           PA7 */
  GPIO_InitStruct.Pin = GPIO_PIN_0|GPIO_PIN_4|GPIO_PIN_5|GPIO_PIN_6
                          |GPIO_PIN_7;
  GPIO_InitStruct.Mode = GPIO_MODE_ANALOG;
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  GPIO_InitStruct.Speed = GPIO_SPEED_FREQ_VERY_HIGH;
  HAL_GPIO_Init(GPIOA, &GPIO_InitStruct);

  /*Configure GPIO pins : PB0 PB1 PB4 PB5
                           PB6 PB7 */
  GPIO_InitStruct.Pin = GPIO_PIN_0|GPIO_PIN_1|GPIO_PIN_4|GPIO_PIN_5
                          |GPIO_PIN_6|GPIO_PIN_7;
  GPIO_InitStruct.Mode = GPIO_MODE_ANALOG;
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
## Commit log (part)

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2020-06-09 Add Schematics
2020-06-12 Work on componant sources
2020-06-12 Work on BOM
2020-06-12 Resistors in 0402
2021-11-05 Move all files in hardware folder
2021-11-05 Change architecture, use NCN5130 instead STKNX
2021-11-07 KnxBoard: Continue with layer 2
2021-11-07 Switch into 4-layers
2021-11-08 Fin de routage
2021-11-08 Pad thermique
2021-11-08 Update serigraphie
2021-11-08 Add text
2021-11-09 Add text for pin background
2021-11-10 Full serigraphie
2021-11-10 update BOM prices by 10
2021-11-10 Add serigraphie and cut edge
2021-11-10 Add MPN in BOM
2021-11-10 Manage Gerber output
2021-11-10 Add SeeedStudio needs file
2021-11-15 Update BOM
2022-07-12 Project: Update to KiCad V6.0
    Add also MCO to debug port (TODO: Need to route)
2022-07-12 Update pcb rules
2022-07-13 Switch to STM32U575CIU6Q MCU
2022-07-13 Add CAD file for SMT32U575CIU6Q
2022-07-13 Create a Roadmap
2022-10-21 New STM32U575CIU6Q
2022-10-21 Create sub-sheet for MCU
2022-10-22 Start new schematics
2022-10-26 Work in progress
2022-10-29 Switch to STM32U575CIT6
2022-11-02 Progress
2022-11-08 Switch to STM32G491KEU6 with NCN5130
2022-11-08 Add 3D model and remove old parts
2022-11-09 Routage OK need check and mass and texts
2022-11-10 Chnage C10 side
2022-11-11 Seed SeeedStudio N°1
2022-11-18 Add submodule for libopencm3 and LightKnxStack
2022-11-18 Start to work on firmware
2022-11-18 First Makefile
2022-11-25 OK for blink test
2022-12-07 State: Led Blink on both Nucleo and KnxBoardV3
2022-12-08 Create structure with HAL
2022-12-09 Removed submodule libopencm3
2023-01-01 Step LED Blink
2023-01-01 Blink also on STM32G4
2023-01-01 Start to write on UART
2023-01-02 Make UART works
2023-01-02 printf and tick OK
2023-01-09 Create CMakeLists.txt with GDB support
2023-01-09 Update KNXBOARDV1
2023-04-15 Manage SDK path
    Now, TTY UART is working
2023-04-19 Configure 38400 Baud, 8 Bit, No parity
2023-04-21 Recive L_Data__ind correctly
2023-04-22 Fix prog_btn, work on P/L connection
2023-11-13 Update schematic
2026-06-09 Route
2026-06-10 Finalize text
2026-06-10 Update size
2026-06-23 Fix Error (First JLCPCB board was fail)
2026-06-23 After review
2026-06-24 Add GND and 3V3 plan in middle layers

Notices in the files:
firmware/Core/KNXBOARDV1/Core/Src/main.c:
Copyright (c) 2023 STMicroelectronics.
All rights reserved.
This software is licensed under terms that can be found in the LICENSE file
